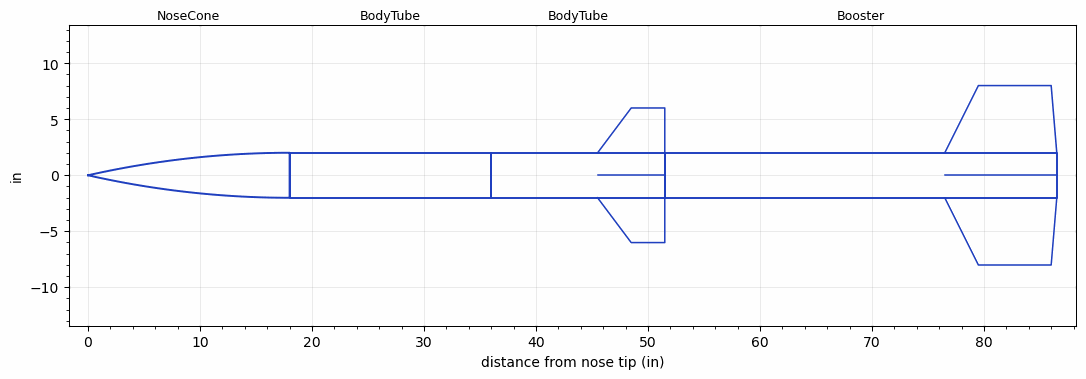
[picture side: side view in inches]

<RASAeroDocument>
 <FileVersion>2</FileVersion>
 <RocketDesign>
  <NoseCone>
   <Length>18</Length>
   <Diameter>4.02</Diameter>
   <Shape>Tangent Ogive</Shape>
   <Location>0</Location>
  </NoseCone>
  <BodyTube>
   <Length>18</Length>
   <Diameter>4.02</Diameter>
   <Location>18</Location>
  </BodyTube>
  <BodyTube>
   <Length>15.5</Length>
   <Diameter>4.02</Diameter>
   <Location>35.9999</Location>
   <Fin>
    <Count>4</Count>
    <Chord>6</Chord>
    <Span>4</Span>
    <SweepDistance>3</SweepDistance>
    <TipChord>3</TipChord>
    <Thickness>0.125</Thickness>
    <Location>6</Location>
    <AirfoilSection>Square</AirfoilSection>
   </Fin>
  </BodyTube>
  <Booster>
   <Length>34.9999</Length>
   <Diameter>4.02</Diameter>
   <Location>51.4999</Location>
   <Fin>
    <Count>4</Count>
    <Chord>10</Chord>
    <Span>6</Span>
    <SweepDistance>3</SweepDistance>
    <TipChord>6.5</TipChord>
    <Thickness>0.375</Thickness>
    <Location>10</Location>
    <AirfoilSection>Square</AirfoilSection>
   </Fin>
  </Booster>
  <Surface>Camouflage Paint</Surface>
  <CD>0</CD>
  <ModifiedBarrowman>False</ModifiedBarrowman>
  <Turbulence>False</Turbulence>
  <UseBooster1>True</UseBooster1>
  <UseBooster2>False</UseBooster2>
 </RocketDesign>
 <LaunchSite>
  <Altitude>0</Altitude>
  <Pressure>29.9214</Pressure>
  <RodAngle>0</RodAngle>
  <RodLength>3.2808</RodLength>
  <Temperature>59</Temperature>
  <WindSpeed>4.4739</WindSpeed>
 </LaunchSite>
 <Recovery>
  <Altitude1>0</Altitude1>
  <Altitude2>0</Altitude2>
  <DeviceType1>None</DeviceType1>
  <DeviceType2>None</DeviceType2>
  <Event1>False</Event1>
  <Event2>False</Event2>
  <Size1>0</Size1>
  <Size2>0</Size2>
  <EventType1>None</EventType1>
  <EventType2>None</EventType2>
  <CD1>0</CD1>
  <CD2>0</CD2>
 </Recovery>
 <SimulationList>
  <Simulation>
   <SustainerLaunchWt>7.7414</SustainerLaunchWt>
   <SustainerCG>36.5811</SustainerCG>
   <SustainerIgnitionDelay>0</SustainerIgnitionDelay>
   <Booster1LaunchWt>20.3581</Booster1LaunchWt>
   <Booster1SeparationDelay>0.3</Booster1SeparationDelay>
   <Booster1IgnitionDelay>0</Booster1IgnitionDelay>
   <Booster1CG>59.2261</Booster1CG>
   <IncludeBooster1>True</IncludeBooster1>
   <Booster2Delay>0</Booster2Delay>
   <IncludeBooster2>False</IncludeBooster2>
  </Simulation>
 </SimulationList>
</RASAeroDocument>
